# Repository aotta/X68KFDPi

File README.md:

# X68KFDPi
Sharp X68000 Floppy disk adapter based on Raspberry Pico(C)

addedd v.1.1: (last night build) - it should improve reading signals and avoid pressing button when floppy inserted (work in progress, for testing purpouse only!)

Use 2 buttons to give X68k the insert/eject signals: you have to eject the virtual floppy (turn off green led) when led flashes, select the image on HxC/Gotek, then re-insert the virtual floppy (Green led re-turned on).
This for disk 1 or 2, as needed.
Now it works for all games i tested so far, but led blinking is not fully supported

Note: use only 74LVC245 IC on your adapter, other type of 74XX245 logic IC may damage your Raspberry!

More info on nfg.forums : [X68KFDUINO - new adapter for external Floppy Drive for HxC & Gotek
](https://nfggames.com/forum2/index.php?topic=7225.0)

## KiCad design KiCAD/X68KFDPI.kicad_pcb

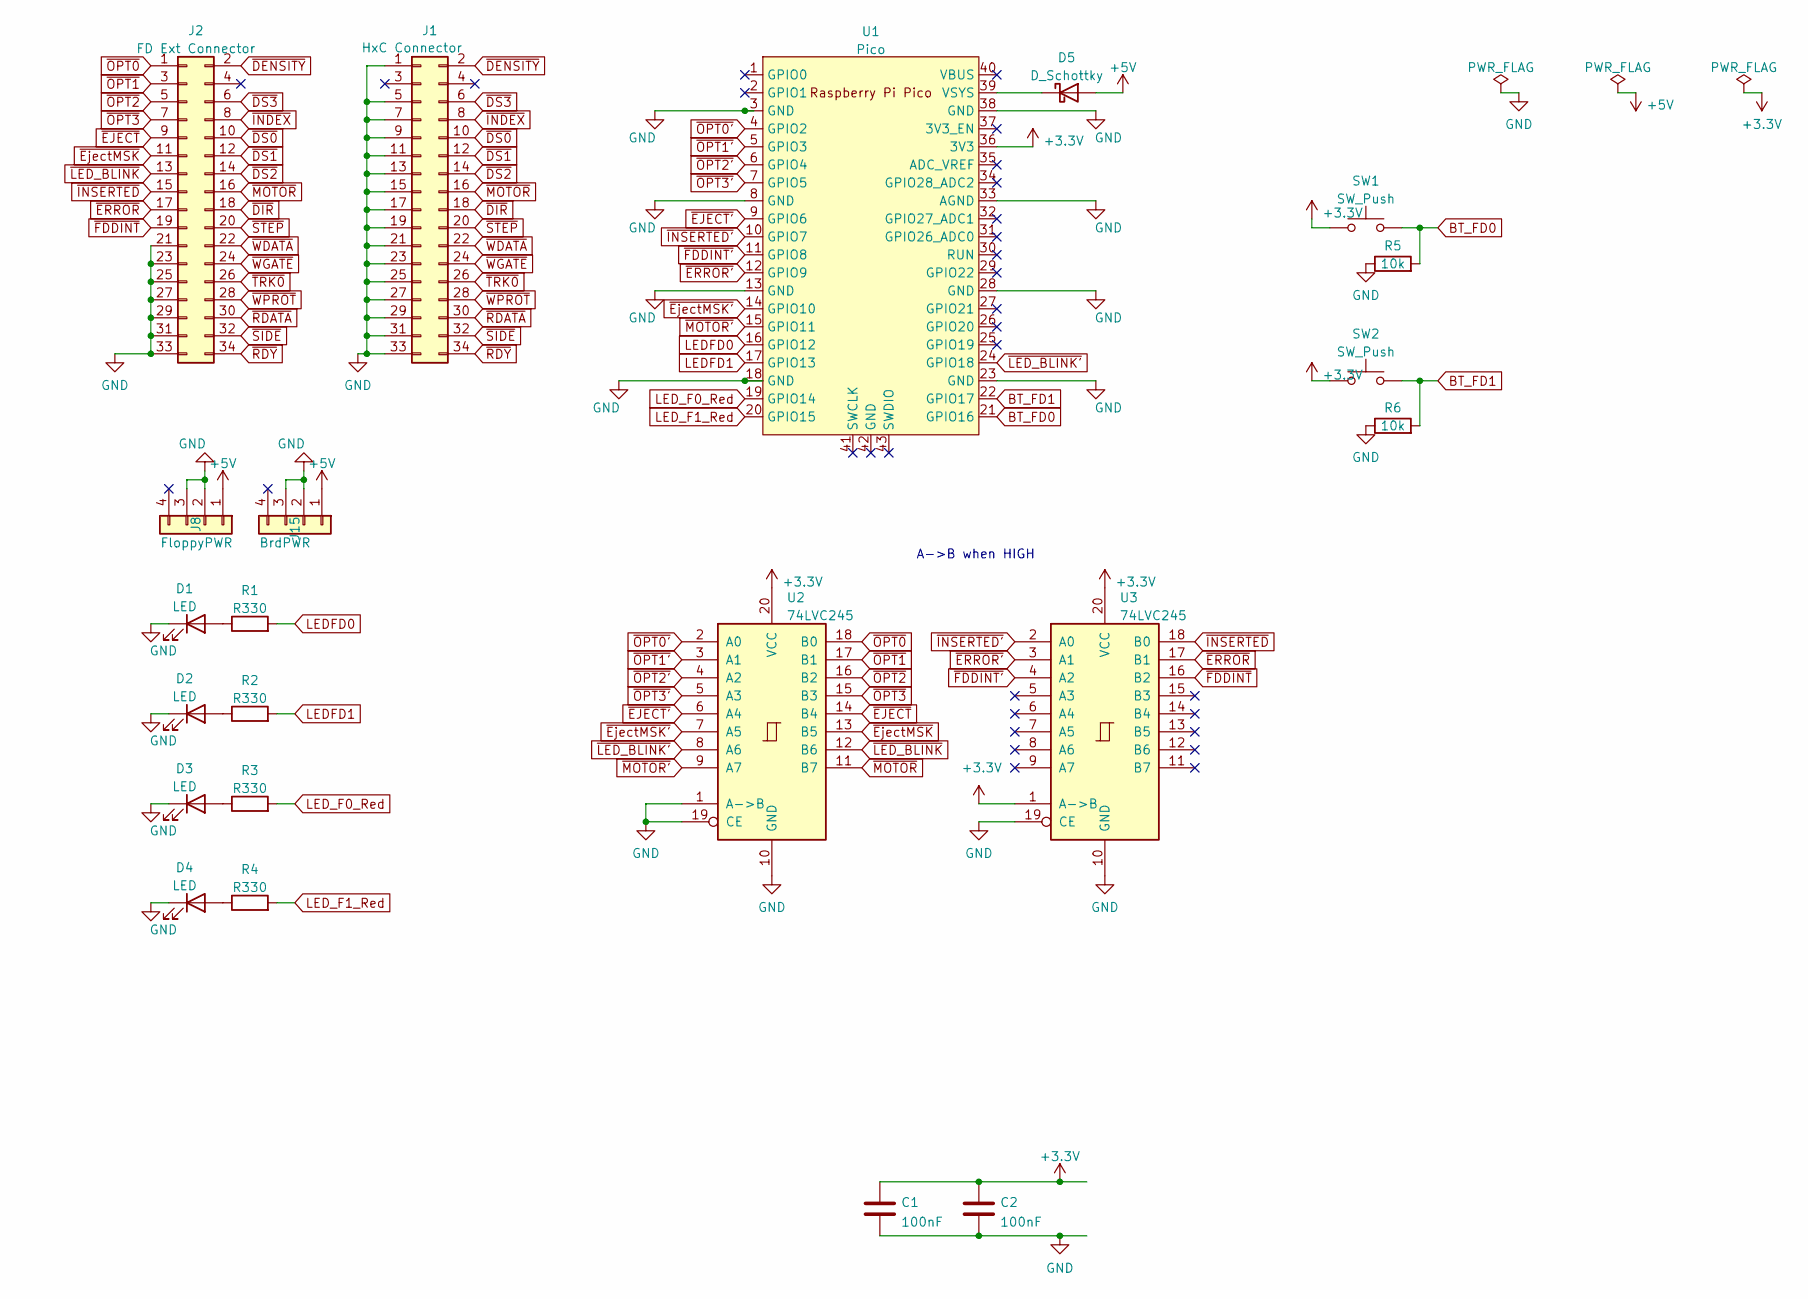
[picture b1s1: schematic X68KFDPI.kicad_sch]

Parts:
C1, C2: 100nF; C_Disc_D3.8mm_W2.6mm_P2.50mm
D1, D2, D3, D4: LED; LED_D3.0mm
D5: D_Schottky; D_DO-15_P12.70mm_Horizontal
J1: HxC Connector; IDC-Header_2x17_P2.54mm_Horizontal
J2: FD Ext Connector; IDC-Header_2x17_P2.54mm_Horizontal
J8: FloppyPWR; PinHeader_1x04_P2.54mm_Horizontal
J15: BrdPWR; PinHeader_1x04_P2.54mm_Horizontal
R1, R2, R3, R4: R330; R_Axial_DIN0207_L6.3mm_D2.5mm_P7.62mm_Horizontal
R5, R6: 10k; R_Axial_DIN0207_L6.3mm_D2.5mm_P7.62mm_Horizontal
SW1, SW2: SW_Push; SW_Tactile_SPST_Angled_PTS645Vx83-2LFS
U1: Pico; RPi_Pico_SMD_TH
U2, U3: 74LVC245; DIP-20_W7.62mm_Socket

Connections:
+3.3V: C1.1, C2.1, SW1.1, SW2.1, U1.36 (3V3), U2.20 (VCC), U3.1 (A->B), U3.20 (VCC)
+5V: D5.2 (A), J8.1, J15.1
BT_FD0: R5.2, SW1.2, U1.21 (GPIO16)
BT_FD1: R6.2, SW2.2, U1.22 (GPIO17)
GND: C1.2, C2.2, D1.1 (K), D2.1 (K), D3.1 (K), D4.1 (K), J1.1, J1.5, J1.7, J1.9, J1.11, J1.13, J1.15, J1.17, J1.19, J1.21, J1.23, J1.25, J1.27, J1.29, J1.31, J1.33, J2.21, J2.23, J2.25, J2.27, J2.29, J2.31, J2.33, J8.2, J8.3, J15.2, J15.3, R5.1, R6.1, U1.3 (GND), U1.8 (GND), U1.13 (GND), U1.18 (GND), U1.23 (GND), U1.28 (GND), U1.33 (AGND), U1.38 (GND), U2.1 (A->B), U2.10 (GND), U2.19 (CE), U3.10 (GND), U3.19 (CE)
LEDFD0: R1.2, U1.16 (GPIO12)
LEDFD1: R2.2, U1.17 (GPIO13)
LED_F0_Red: R3.2, U1.19 (GPIO14)
LED_F1_Red: R4.2, U1.20 (GPIO15)
unnamed: D1.2 (A), R1.1
unnamed: D2.2 (A), R2.1
unnamed: D3.2 (A), R3.1
unnamed: D4.2 (A), R4.1
unnamed: D5.1 (K), U1.39 (VSYS)
~DENSITY: J1.2, J2.2
~DIR: J1.18, J2.18
~DS0: J1.10, J2.10
~DS1: J1.12, J2.12
~DS2: J1.14, J2.14
~DS3: J1.6, J2.6
~EJECT': U1.9 (GPIO6), U2.6 (A4)
~EJECT: J2.9, U2.14 (B4)
~ERROR': U1.12 (GPIO9), U3.3 (A1)
~ERROR: J2.17, U3.17 (B1)
~EjectMSK': U1.14 (GPIO10), U2.7 (A5)
~EjectMSK: J2.11, U2.13 (B5)
~FDDINT': U1.11 (GPIO8), U3.4 (A2)
~FDDINT: J2.19, U3.16 (B2)
~INDEX: J1.8, J2.8
~INSERTED': U1.10 (GPIO7), U3.2 (A0)
~INSERTED: J2.15, U3.18 (B0)
~LED_BLINK': U1.24 (GPIO18), U2.8 (A6)
~LED_BLINK: J2.13, U2.12 (B6)
~MOTOR': U1.15 (GPIO11), U2.9 (A7)
~MOTOR: J1.16, J2.16, U2.11 (B7)
~OPT0': U1.4 (GPIO2), U2.2 (A0)
~OPT0: J2.1, U2.18 (B0)
~OPT1': U1.5 (GPIO3), U2.3 (A1)
~OPT1: J2.3, U2.17 (B1)
~OPT2': U1.6 (GPIO4), U2.4 (A2)
~OPT2: J2.5, U2.16 (B2)
~OPT3': U1.7 (GPIO5), U2.5 (A3)
~OPT3: J2.7, U2.15 (B3)
~RDATA: J1.30, J2.30
~RDY: J1.34, J2.34
~SIDE: J1.32, J2.32
~STEP: J1.20, J2.20
~TRK0: J1.26, J2.26
~WDATA: J1.22, J2.22
~WGATE: J1.24, J2.24
~WPROT: J1.28, J2.28

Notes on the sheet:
A->B when HIGH

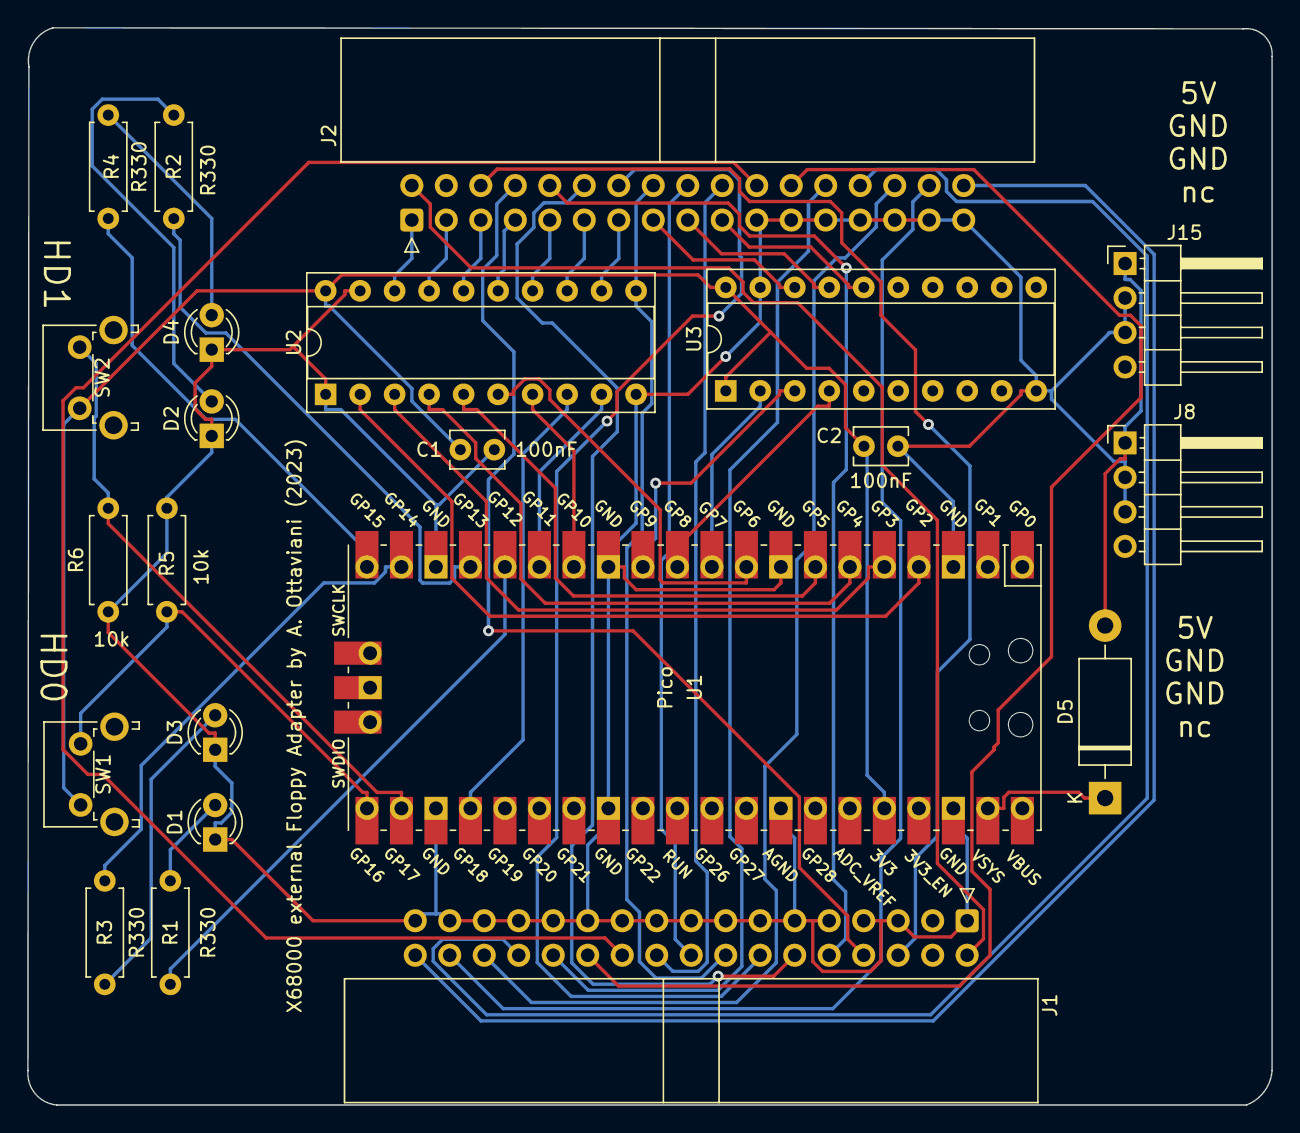
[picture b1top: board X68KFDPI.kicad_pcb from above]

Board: 2 copper layers, 91.6 x 79.3 mm, 22 parts (0 on the bottom side), 51 nets.

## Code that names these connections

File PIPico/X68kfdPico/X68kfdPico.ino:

/*
 * X68KFDINO - External FD adapter for Sharp X68000
 * by Andrea Ottaviani june 2023
 * 
 * 
Access/Write strobe :

/OPTION_SEL_X : "Chip select" for the extra functions of drive DSX (X: 0-3)

Input / functions signals :

/EJECT_FUNC : If this signal is low when OPTION_SEL_X is asserted, the disk will be ejected.
/LOCK_FUNC (Eject MSK?): If this signal is low when OPTION_SEL_X is asserted, the disk will be locked (eject button off). If this signal is high when OPTION_SEL_X is asserted the disk will be unlocked (eject button on).
/BLINK_FUNC : If this signal is low when OPTION_SEL_X is asserted, the LED blink. If this signal is high when OPTION_SEL_X is asserted, the LED stop blinking.

Output signals (drive status):

/DISK_IN_DRIVE : when OPTION_SEL_X is asserted : Low = a disk in the drive. High = No disk.
/INSERT_FAULT : when OPTION_SEL_X is asserted : Low = a disk insert failure occured . High = No problem. This status is cleared at the rising edge of OPTION_SEL_X.

Output signal (Interrupt line):

/INT : Interrupt line : This signal is activated at each disk status change (inserted/ejected). The interrupt is cleared at the rising edge of /OPTION_SEL_X. (Note : more than one drive can activate this line in the same time -> Softwares scan all disk drive at each /INT assertion).

Note 1: For proper operation all output should be able to drive 5/150=33mA since 150 ohms pull-up are used.
Note 2: The X68000 /OPTION_SEL_X assertion duration is ~2.5us per access. This can depend of the software, the CPU speed.
 */


//Cablage
#define OPT0                2  // Set D2 as OPT0 Read strobe
#define OPT1                3  // Set D3 as OPT1 Read strobe
#define OPT2                4  // Set D4 as OPT2 Read strobe
#define OPT3                5  // Set D5 as OPT3 Read strobe
#define Eject               6  // Set D6 as Eject Read strobe
#define Inserted            7  // Set D7 as Inserted Read strobe
#define FDDINT              8  // Set D8 as FD Interrupt Read strobe
#define Error               9  // Set D9 as Error Read strobe
#define EjectMSK           10  // Set D10 as EjectMSK Read strobe
#define Motor              11  // Set D11 as Motor Read strobe
#define LEDFD0             12  // Set D12 as LED FD0 output (Green LED)
#define LEDFD1             13  // Set D13 as LED FD1 output (Green LED)
#define LED_FD0_RED        14  // Set D14 as LED FD0 output (Red LED)
#define LED_FD1_RED        15  // Set D15 as LED FD1 output (Red LED)
#define BT_FD0             16  // Set D16 as Button FD0 Read strobe
#define BT_FD1             17  // Set D17 as Button FD1 Read strobe
#define LED_BLINK          18  // Set A0 as LED (Blink) output


void setup() {
  // put your setup code here, to run once:
  // initialize digital pin 13 as an output.
  pinMode(OPT0, INPUT);
  pinMode(OPT1, INPUT);
  pinMode(OPT2, INPUT);
  pinMode(OPT3, INPUT);
  pinMode(Eject, INPUT);
  pinMode(BT_FD0, INPUT);
  pinMode(BT_FD1, INPUT);
  pinMode(LED_BLINK, INPUT); // Blink
  pinMode(EjectMSK, INPUT); // LOCK (Red led)
  pinMode(Motor, INPUT); // 
  pinMode(Inserted, OUTPUT);
  pinMode(Error, OUTPUT);
  pinMode(FDDINT, OUTPUT);
  pinMode(LEDFD0, OUTPUT);
  pinMode(LEDFD1, OUTPUT);
  pinMode(LED_FD0_RED, OUTPUT); // used for LED LOCK, Red light
  pinMode(LED_FD1_RED, OUTPUT); // used for LED LOCK, Red light
  
  Serial.begin(115200);

}

void loop() {
  unsigned char DF0=1; // 0=eject, 1=insert, 2=lock, 3=blink
  unsigned char DF1=1; // 0=eject, 1=insert, 2=lock, 3=blink
  unsigned char bitBlink=0;
  unsigned short int BlinkCounter=0;
   
  // put your main code here, to run repeatedly:
 Serial.println("Start");
 while(1) {

    BlinkCounter++;
    if (BlinkCounter>=29999) BlinkCounter=0;
    
    if (digitalRead(BT_FD0)) {
       if (DF0==1) {
        DF0=0;
      } else {
        bitBlink=0;
        DF0=1;
       }
    Serial.print("DF0:");Serial.println(DF0);
    delay(200);
    digitalWrite(FDDINT,LOW);
    }

  if (digitalRead(BT_FD1)) {
       if (DF1==1) {
        DF1=0;
      } else {
        bitBlink=0;
        DF1=1;
      }
    Serial.print("DF1:");Serial.println(DF1);
    delay(200);
    digitalWriteFast(FDDINT,LOW);
    }

  if (!digitalReadFast(LED_BLINK)) {
       bitBlink=1;
     // Serial.print("Led Blink");
      }    

  if (!digitalReadFast(OPT0)) {
  
    
     if (!digitalReadFast(Eject)) {
       DF0=0;
       digitalWriteFast(FDDINT,LOW);
    //   Serial.print("Ej 0-");
    }
 
    if (!DF0) {
        digitalWriteFast(LEDFD0,LOW);
        digitalWriteFast(Inserted,HIGH);  // for TT!!        
      } else {
        digitalWriteFast(Inserted,LOW);
         digitalWriteFast(Error,HIGH);  
         digitalWriteFast(FDDINT,HIGH);  // not remove!! 
         digitalWriteFast(LEDFD0,HIGH);
      }

    if (!digitalReadFast(EjectMSK)) {
      digitalWriteFast(LED_FD0_RED,HIGH);
    //   Serial.print("EjMSK 0-");
      } else {
      digitalWriteFast(LED_FD0_RED,LOW);
    }

 }  // opt 0

 if (!digitalReadFast(OPT1)) {
 
  if (!(digitalReadFast(Eject))) {
      DF1=0;
      digitalWriteFast(FDDINT,LOW);
  //    Serial.print("Ej 1-");
    }
     
   if (!DF1) {
        digitalWriteFast(LEDFD1,LOW);
        digitalWriteFast(Inserted,HIGH);  // for TT!!        
      } else {
        digitalWriteFast(Inserted,LOW);
         digitalWriteFast(Error,HIGH);  
         digitalWriteFast(FDDINT,HIGH);  // not remove!! 
         digitalWriteFast(LEDFD1,HIGH);
      }

    if (!digitalReadFast(EjectMSK)) {
      digitalWriteFast(LED_FD1_RED,HIGH);
     // Serial.print("EjMSK 1-");
      } else {
      digitalWriteFast(LED_FD1_RED,LOW);
    }

  } //opt1

  if (bitBlink==1) {
    if (!DF0) {
       Serial.print("b0"); // do not remove, needed for timing

      if (BlinkCounter>=3000) {
        digitalWriteFast(LEDFD0,LOW);
      } else {
        digitalWriteFast(LEDFD0,HIGH);
      }
    }
    if (!DF1) {
      Serial.print("b1"); // do not remove, needed for timing
    if (BlinkCounter>=3000) {
        digitalWriteFast(LEDFD1,LOW);
      } else {
        digitalWriteFast(LEDFD1,HIGH);
      }
    }
  }
  
 } //while
 
}
